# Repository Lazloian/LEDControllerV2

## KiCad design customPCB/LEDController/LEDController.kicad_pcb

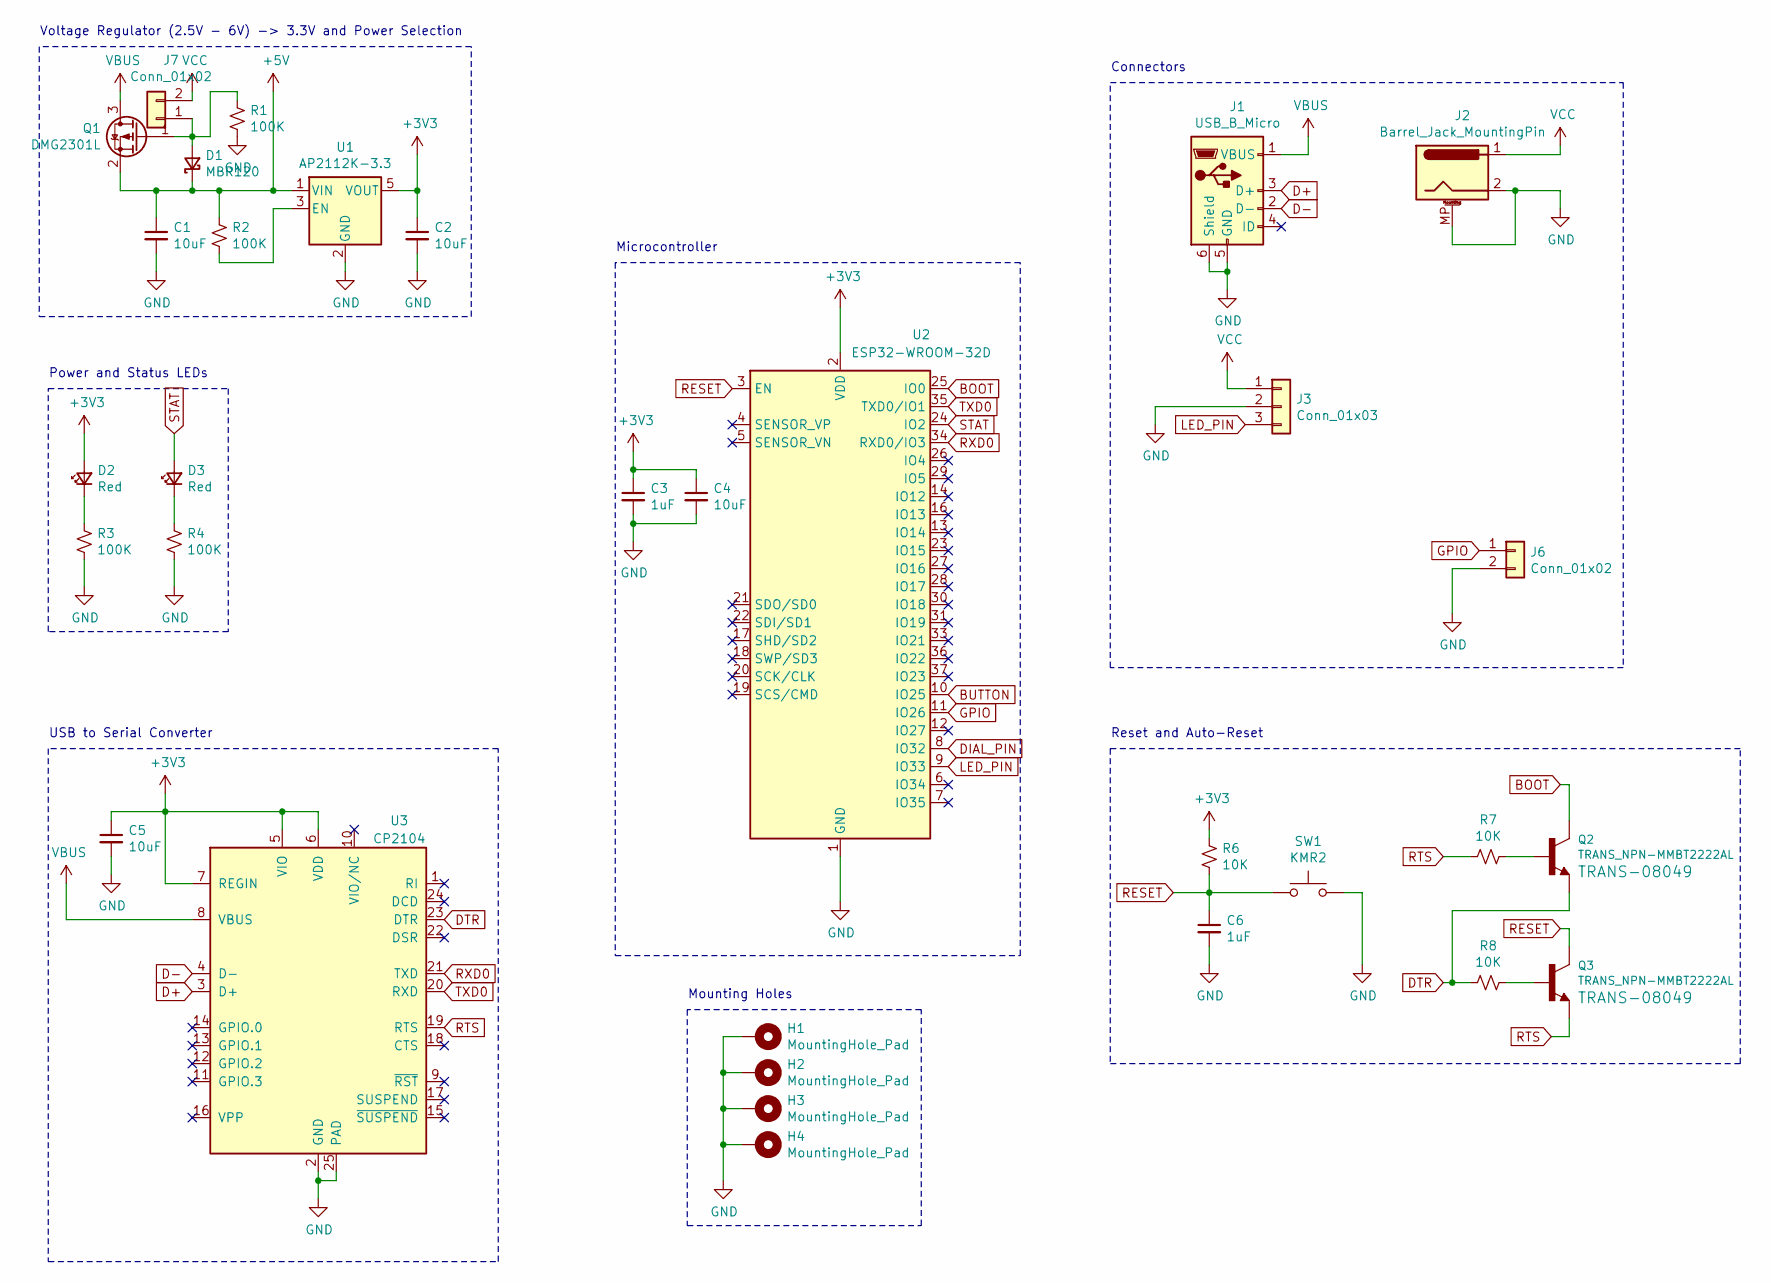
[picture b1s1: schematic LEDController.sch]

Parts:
C1, C2, C4, C5: 10uF; C_0603_1608Metric
C3, C6: 1uF; C_0603_1608Metric
D1: MBR120; D_SOD-123F
D2, D3: Red; LED_0603_1608Metric
H1, H2, H3, H4: MountingHole_Pad; MountingHole_3.2mm_M3_Pad_Via
J1: USB_B_Micro; USB_Micro-B_Amphenol_10103594-0001LF_Horizontal
J2: Barrel_Jack_MountingPin; BarrelJack_CUI_PJ-063AH_Horizontal
J3: Conn_01x03; PinHeader_1x03_P2.54mm_Vertical
J6, J7: Conn_01x02; PinHeader_1x02_P2.54mm_Vertical
Q1: DMG2301L; SOT-23
Q2, Q3: TRANS_NPN-MMBT2222AL; SOT23-3
R1, R2, R3, R4: 100K; R_0603_1608Metric
R6, R7, R8: 10K; R_0603_1608Metric
SW1: KMR2; SW_Push_1P1T_NO_CK_KMR2
U1: AP2112K-3.3; SOT-23-5
U2: ESP32-WROOM-32D; ESP32-WROOM-32
U3: CP2104; QFN-24-1EP_4x4mm_P0.5mm_EP2.6x2.6mm

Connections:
+3V3: C2.1, C3.1, C4.1, C5.1, D2.2 (A), R6.1, U1.5 (VOUT), U2.2 (VDD), U3.5 (VIO), U3.6 (VDD), U3.7 (REGIN)
+5V: C1.1, D1.1 (K), Q1.2 (S), R2.1, U1.1 (VIN)
BOOT: Q2.3 (C), U2.25 (IO0)
BUTTON: U2.10 (IO25)
D+: J1.3 (D+), U3.3 (D+)
D-: J1.2 (D-), U3.4 (D-)
DIAL_PIN: U2.8 (IO32)
DTR: Q2.2 (E), R8.2, U3.23 (DTR)
GND: C1.2, C2.2, C3.2, C4.2, C5.2, C6.2, H1.1, H2.1, H3.1, H4.1, J1.5 (GND), J1.6 (Shield), J2.2, J2.MP (MountPin), J3.2, J6.2, R1.2, R3.2, R4.2, SW1.2, U1.2 (GND), U2.1 (GND), U2.15 (GND), U2.38 (GND), U2.39 (GND), U3.2 (GND), U3.25 (PAD)
GPIO: J6.1, U2.11 (IO26)
LED_PIN: J3.3, U2.9 (IO33)
unnamed: D1.2 (A), J7.1, Q1.1 (G), R1.1
unnamed: D2.1 (K), R3.1
unnamed: D3.1 (K), R4.1
unnamed: Q2.1 (B), R7.1
unnamed: Q3.1 (B), R8.1
unnamed: R2.2, U1.3 (EN)
RESET: C6.1, Q3.3 (C), R6.2, SW1.1, U2.3 (EN)
RTS: Q3.2 (E), R7.2, U3.19 (RTS)
RXD0: U2.34 (RXD0/IO3), U3.21 (TXD)
STAT: D3.2 (A), U2.24 (IO2)
TXD0: U2.35 (TXD0/IO1), U3.20 (RXD)
VBUS: J1.1 (VBUS), Q1.3 (D), U3.8 (VBUS)
VCC: J2.1, J3.1, J7.2

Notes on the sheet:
Voltage Regulator (2.5V - 6V) -> 3.3V and Power Selection
Reset and Auto-Reset
USB to Serial Converter
Microcontroller
Power and Status LEDs
Connectors
Mounting Holes

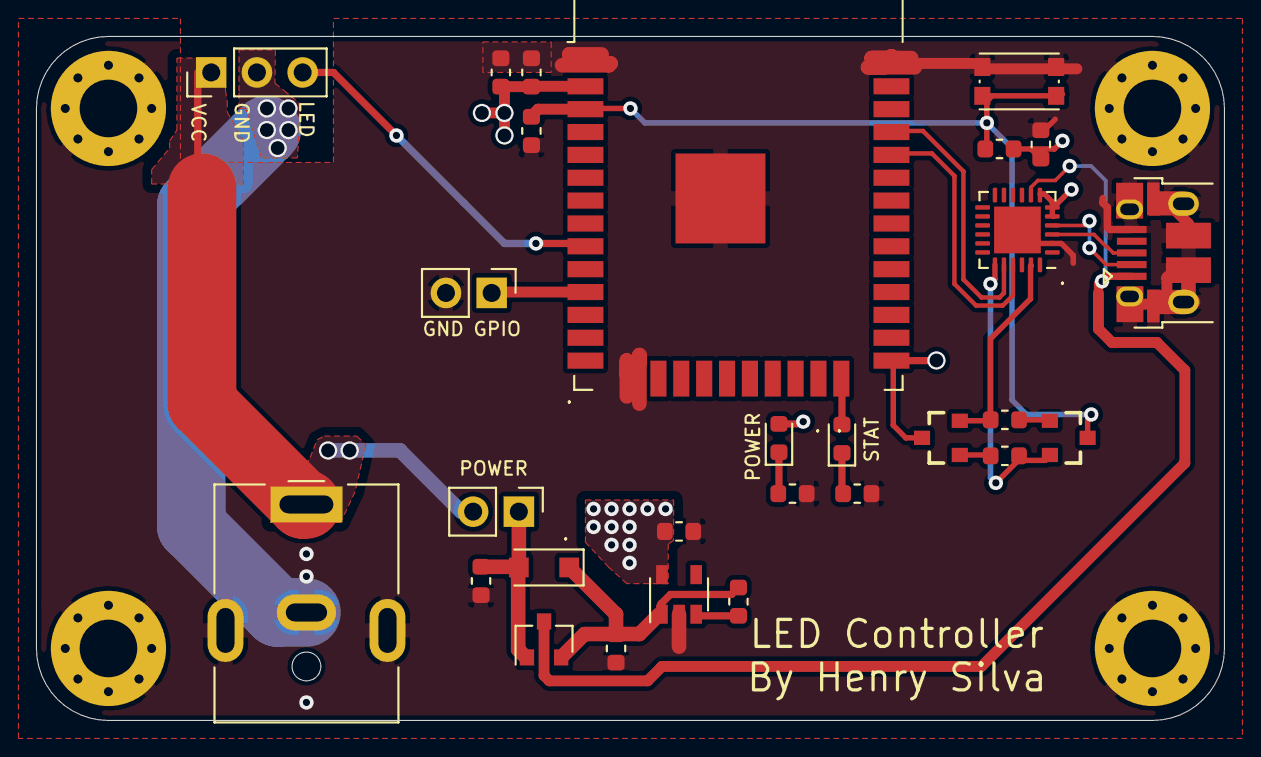
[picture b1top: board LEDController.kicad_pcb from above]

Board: 2 copper layers, 66.0 x 38.0 mm, 32 parts (0 on the bottom side), 22 nets.

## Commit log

2020-05-20 added android app
2020-05-22 implemented EventBus
2020-05-23 added one button BT connect
2020-05-24 added connect button results to user
2020-05-25 added connection updater
2020-05-27 added room database
2020-06-01 simple color sending
2020-06-03 added simple color creation
2020-06-05 added fade
2020-06-07 fixed led freezing
2020-06-10 added flow
2020-06-12 added edit to app
2020-06-14 added brightness setting
2020-06-17 added kiCAD project
2020-06-19 added board design
2020-06-24 added off button
